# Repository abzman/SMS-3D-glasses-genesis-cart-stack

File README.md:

# SMS-3D-glasses-genesis-cart-stack
pass-through adapter to add 3d glasses support to a genesis running master system software

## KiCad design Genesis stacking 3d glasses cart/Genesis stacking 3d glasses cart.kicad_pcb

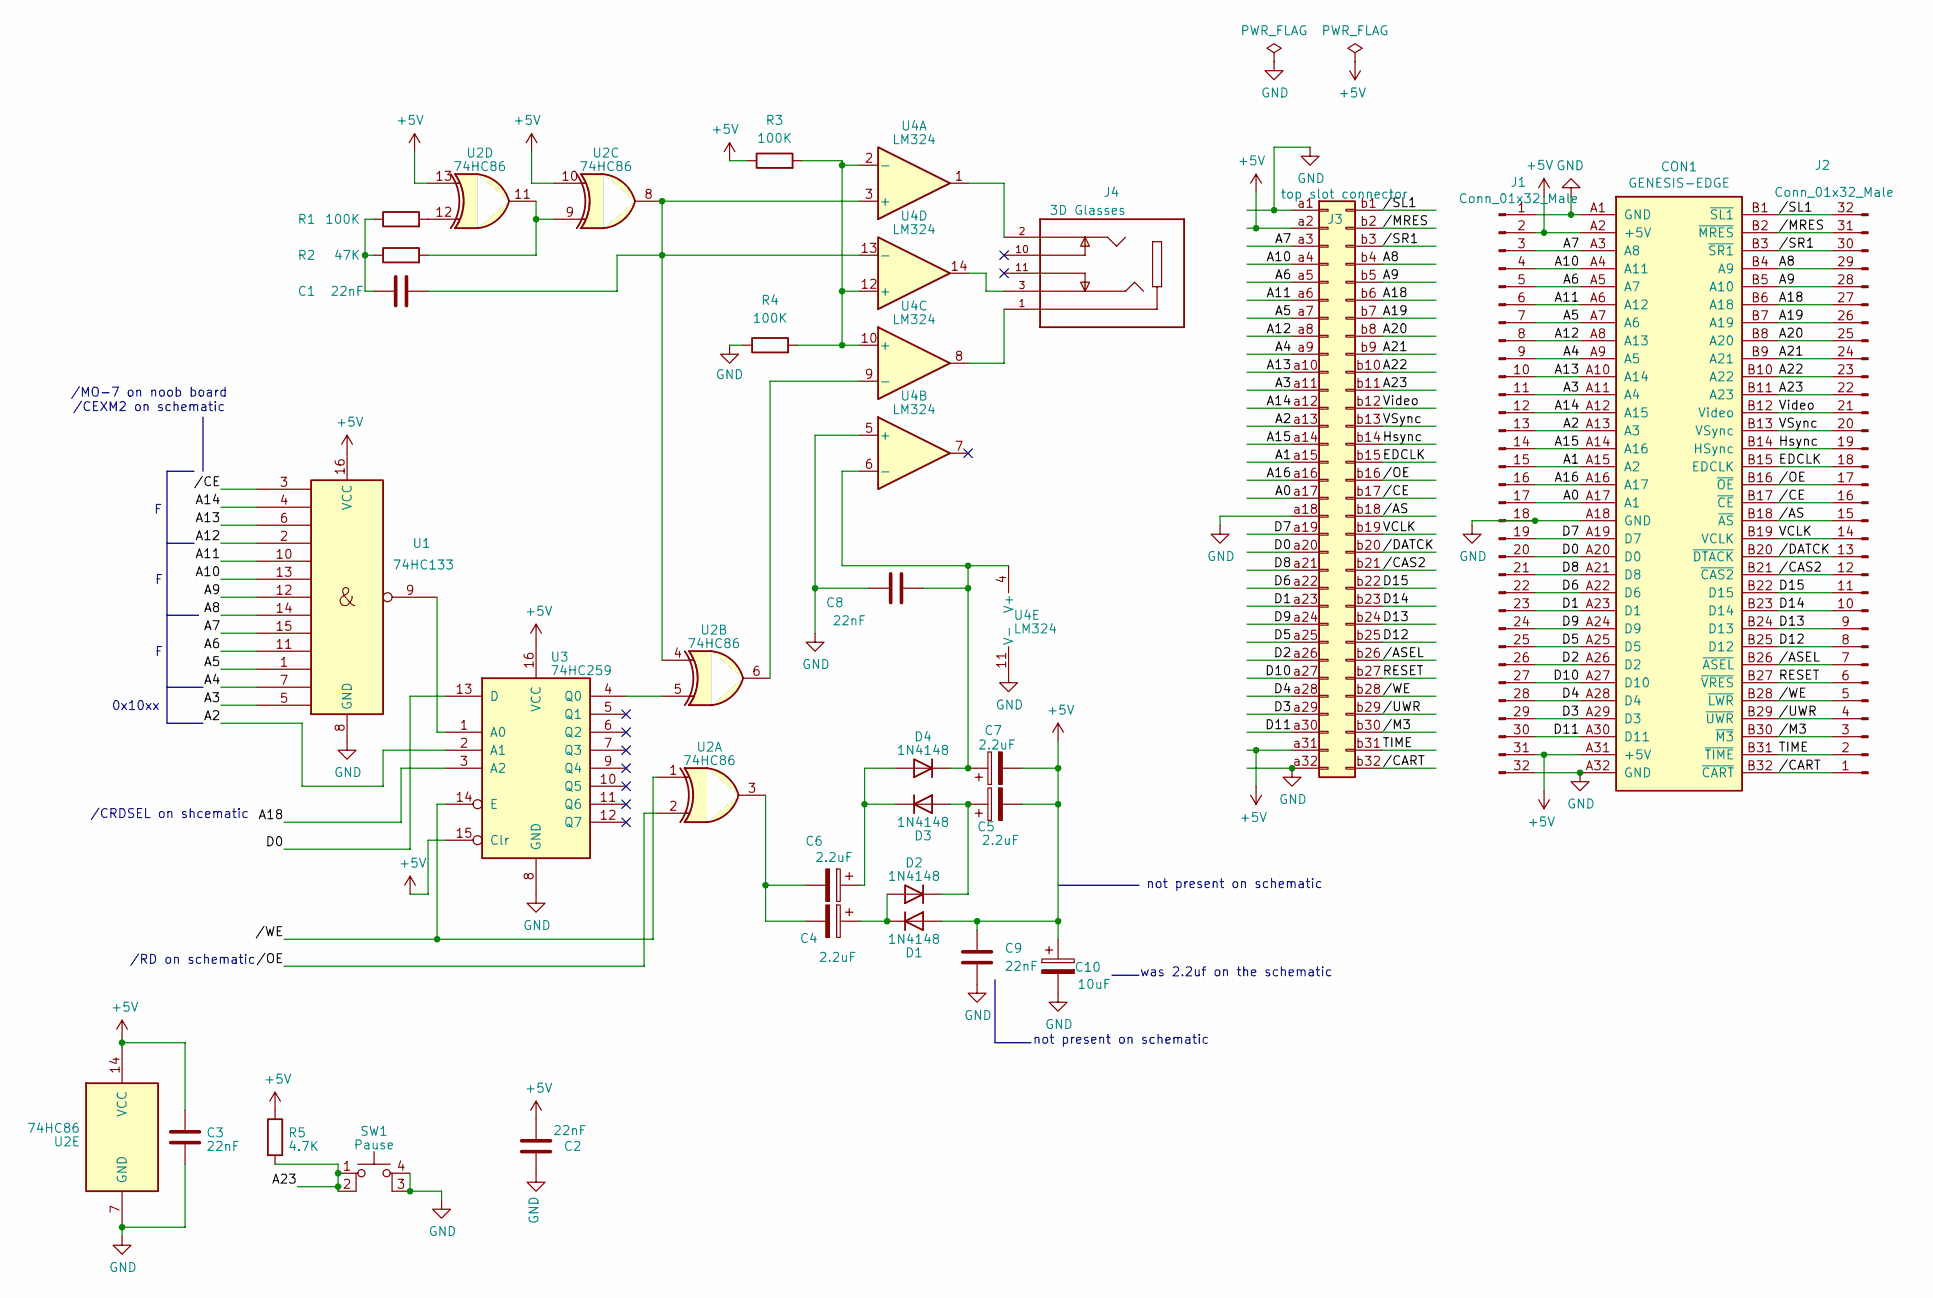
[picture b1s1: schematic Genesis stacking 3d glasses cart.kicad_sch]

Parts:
C1, C2, C3, C8, C9: 22nF; C_0603_1608Metric
C4, C5, C6, C7: 2.2uF; CP_Radial_D5.0mm_P2.50mm
C10: 10uF; CP_Radial_D5.0mm_P2.50mm
CON1: GENESIS-EDGE
D1, D2, D3, D4: 1N4148; D_SOD-123F
J1, J2: Conn_01x32_Male; PinSocket_1x32_P2.54mm_Vertical
J3: top slot connector; Genesis cart edge mount connector
J4: 3D Glasses; CUI_SJ1-3525N; PARTREV 1.02
R1, R3, R4: 100K; R_0603_1608Metric
R2: 47K; R_0603_1608Metric
R5: 4.7K; R_0603_1608Metric
SW1: Pause; SW_SPST_Omron_B3FS-105xP
U1: 74HC133; SOIC-16_3.9x9.9mm_P1.27mm
U2: 74HC86; SOIC-14_3.9x8.7mm_P1.27mm
U3: 74HC259; SOIC-16_3.9x9.9mm_P1.27mm
U4: LM324; SOIC-14_3.9x8.7mm_P1.27mm

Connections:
+5V: C2.1, C3.2, C5.2, C7.2, C9.2, C10.1, CON1.A2 (+5V), CON1.A31 (+5V), D1.2 (A), J1.2, J1.31, J3.a2, J3.a31, R3.1, R5.1, U1.16 (VCC), U2.10, U2.13, U2.14 (VCC), U3.15 (Clr), U3.16 (VCC)
/A0: CON1.A17 (A1), J1.17, J3.a17
/A1: CON1.A15 (A2), J1.15, J3.a15
/A2: CON1.A13 (A3), J1.13, J3.a13, U3.2 (A1)
/A3: CON1.A11 (A4), J1.11, J3.a11, U1.5
/A4: CON1.A9 (A5), J1.9, J3.a9, U1.7
/A5: CON1.A7 (A6), J1.7, J3.a7, U1.1
/A6: CON1.A5 (A7), J1.5, J3.a5, U1.11
/A7: CON1.A3 (A8), J1.3, J3.a3, U1.15
/A8: CON1.B4 (A9), J2.29, J3.b4, U1.14
/A9: CON1.B5 (A10), J2.28, J3.b5, U1.12
/A10: CON1.A4 (A11), J1.4, J3.a4, U1.13
/A11: CON1.A6 (A12), J1.6, J3.a6, U1.10
/A12: CON1.A8 (A13), J1.8, J3.a8, U1.2
/A13: CON1.A10 (A14), J1.10, J3.a10, U1.6
/A14: CON1.A12 (A15), J1.12, J3.a12, U1.4
/A15: CON1.A14 (A16), J1.14, J3.a14
/A16: CON1.A16 (A17), J1.16, J3.a16
/A18: CON1.B6 (A18), J2.27, J3.b6, U3.3 (A2)
/A19: CON1.B7 (A19), J2.26, J3.b7
/A20: CON1.B8 (A20), J2.25, J3.b8
/A21: CON1.B9 (A21), J2.24, J3.b9
/A22: CON1.B10 (A22), J2.23, J3.b10
/A23: CON1.B11 (A23), J2.22, J3.b11, R5.2, SW1.1, SW1.2
/D0: CON1.A20 (D0), J1.20, J3.a20, U3.13 (D)
/D1: CON1.A23 (D1), J1.23, J3.a23
/D2: CON1.A26 (D2), J1.26, J3.a26
/D3: CON1.A29 (D3), J1.29, J3.a29
/D4: CON1.A28 (D4), J1.28, J3.a28
/D5: CON1.A25 (D5), J1.25, J3.a25
/D6: CON1.A22 (D6), J1.22, J3.a22
/D7: CON1.A19 (D7), J1.19, J3.a19
/D8: CON1.A21 (D8), J1.21, J3.a21
/D9: CON1.A24 (D9), J1.24, J3.a24
/D10: CON1.A27 (D10), J1.27, J3.a27
/D11: CON1.A30 (D11), J1.30, J3.a30
/D12: CON1.B25 (D12), J2.8, J3.b25
/D13: CON1.B24 (D13), J2.9, J3.b24
/D14: CON1.B23 (D14), J2.10, J3.b23
/D15: CON1.B22 (D15), J2.11, J3.b22
/EDCLK: CON1.B15 (EDCLK), J2.18, J3.b15
/Hsync: CON1.B14 (HSync), J2.19, J3.b14
/RESET: CON1.B27 (~VRES), J2.6, J3.b27
/TIME: CON1.B31 (~TIME), J2.2, J3.b31
/VCLK: CON1.B19 (VCLK), J2.14, J3.b19
/VSync: CON1.B13 (VSync), J2.20, J3.b13
/Video: CON1.B12 (Video), J2.21, J3.b12
//AS: CON1.B18 (~AS), J2.15, J3.b18
//ASEL: CON1.B26 (~ASEL), J2.7, J3.b26
//CART: CON1.B32 (~CART), J2.1, J3.b32
//CAS2: CON1.B21 (~CAS2), J2.12, J3.b21
//CE: CON1.B17 (~CE), J2.16, J3.b17, U1.3
//DATCK: CON1.B20 (~DTACK), J2.13, J3.b20
//M3: CON1.B30 (~M3), J2.3, J3.b30
//MRES: CON1.B2 (~MRES), J2.31, J3.b2
//OE: CON1.B16 (~OE), J2.17, J3.b16, U2.2
//SL1: CON1.B1 (~SL1), J2.32, J3.b1
//SR1: CON1.B3 (~SR1), J2.30, J3.b3
//UWR: CON1.B29 (~UWR), J2.4, J3.b29
//WE: CON1.B28 (~LWR), J2.5, J3.b28, U2.1, U3.14 (E)
GND: C2.2, C3.1, C8.1, C9.1, C10.2, CON1.A1 (GND), CON1.A18 (GND), CON1.A32 (GND), J1.1, J1.18, J1.32, J3.a1, J3.a18, J3.a32, R4.1, SW1.3 (K), SW1.4 (A), U1.8 (GND), U2.7 (GND), U3.8 (GND), U4.5 (+), U4.11 (V-)
unnamed: C1.1, R1.1, R2.1
unnamed: C4.2, C6.2, U2.3
unnamed: C4.1, D1.1 (K), D2.2 (A)
unnamed: C5.1, D2.1 (K), D3.2 (A)
unnamed: C6.1, D3.1 (K), D4.2 (A)
unnamed: C7.1, C8.2, D4.1 (K), U4.4 (V+), U4.6 (-)
unnamed: J4.1, U4.8
unnamed: J4.2, U4.1
unnamed: J4.3, U4.14
unnamed: R1.2, U2.12
unnamed: R2.2, U2.9, U2.11
unnamed: U1.9, U3.1 (A0)
unnamed: U2.5, U3.4 (Q0)
unnamed: C1.2, U2.4, U2.8, U4.3 (+), U4.13 (-)
unnamed: R3.2, R4.2, U4.2 (-), U4.10 (+), U4.12 (+)
unnamed: U2.6, U4.9 (-)

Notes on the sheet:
/MO-7 on noob board /CEXM2 on schematic
/CRDSEL on shcematic
/RD on schematic
0x10xx
was 2.2uf on the schematic
not present on schematic

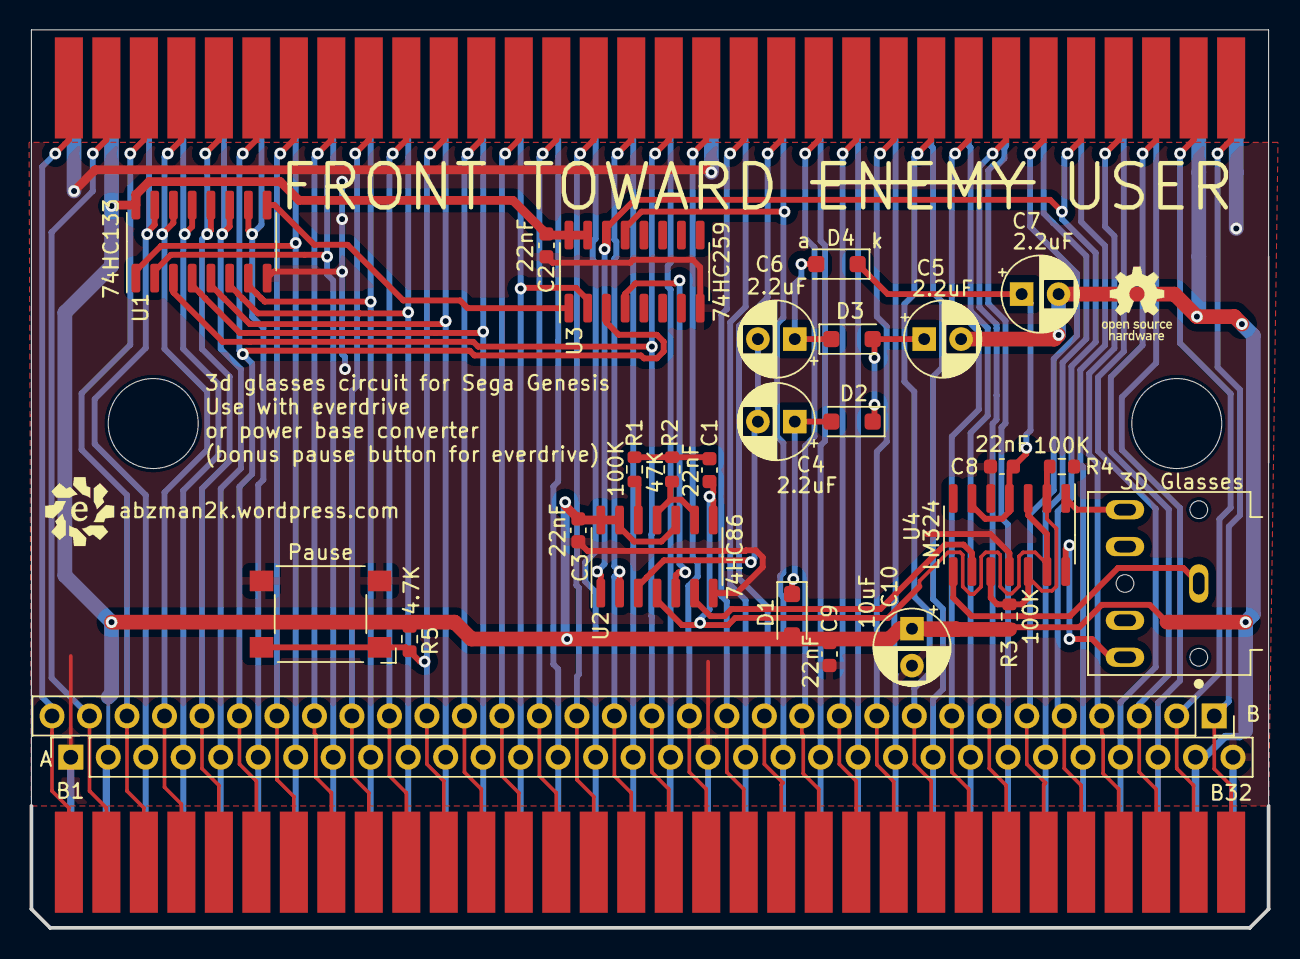
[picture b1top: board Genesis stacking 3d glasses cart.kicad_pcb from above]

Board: 2 copper layers, 83.8 x 60.7 mm, 29 parts (0 on the bottom side), 77 nets.

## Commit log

2023-04-22 added initial layout, no chips routed, gonna try DIP
2023-04-24 added PTH version based on the incorrect schematic and the mostly SMD version based on the reverse engineered board someone made and tested.
2024-01-18 added images
2024-07-29 updated silk
2026-02-04 updated design, added reference materials
2026-02-06 looks like last revision before fab
2026-02-11 changes from ordering the pcb
